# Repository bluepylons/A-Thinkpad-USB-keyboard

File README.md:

# Work in Progress

## Note January 21, 2025: the downstream USB-C port likely violates USB-C spec since it provides 5V all the time, instead of only when CC resistors are detected.

# About

This is a project attempting to make a USB keyboard/Trackpoint controller and enclosure for the non-chiclet Thinkpad keyboard (from the 10/20 generation, such as the T410, W520, etc.). These were, in my opinion, the best Thinkpad keyboards ever made.

# Controller

The current plan is to use an RP2040 microcontroller running QMK to handle the key matrix scanning and Trackpoint. I would also like to add a USB 2.0 hub.

# Future goals

I would like to eventually adapt this keyboard to be used on the Framework 13 laptop, which would require designing a custom lower chassis for the Framework laptop. That is well in the future, but the engineering required for this project lays much of the groundwork for that project.

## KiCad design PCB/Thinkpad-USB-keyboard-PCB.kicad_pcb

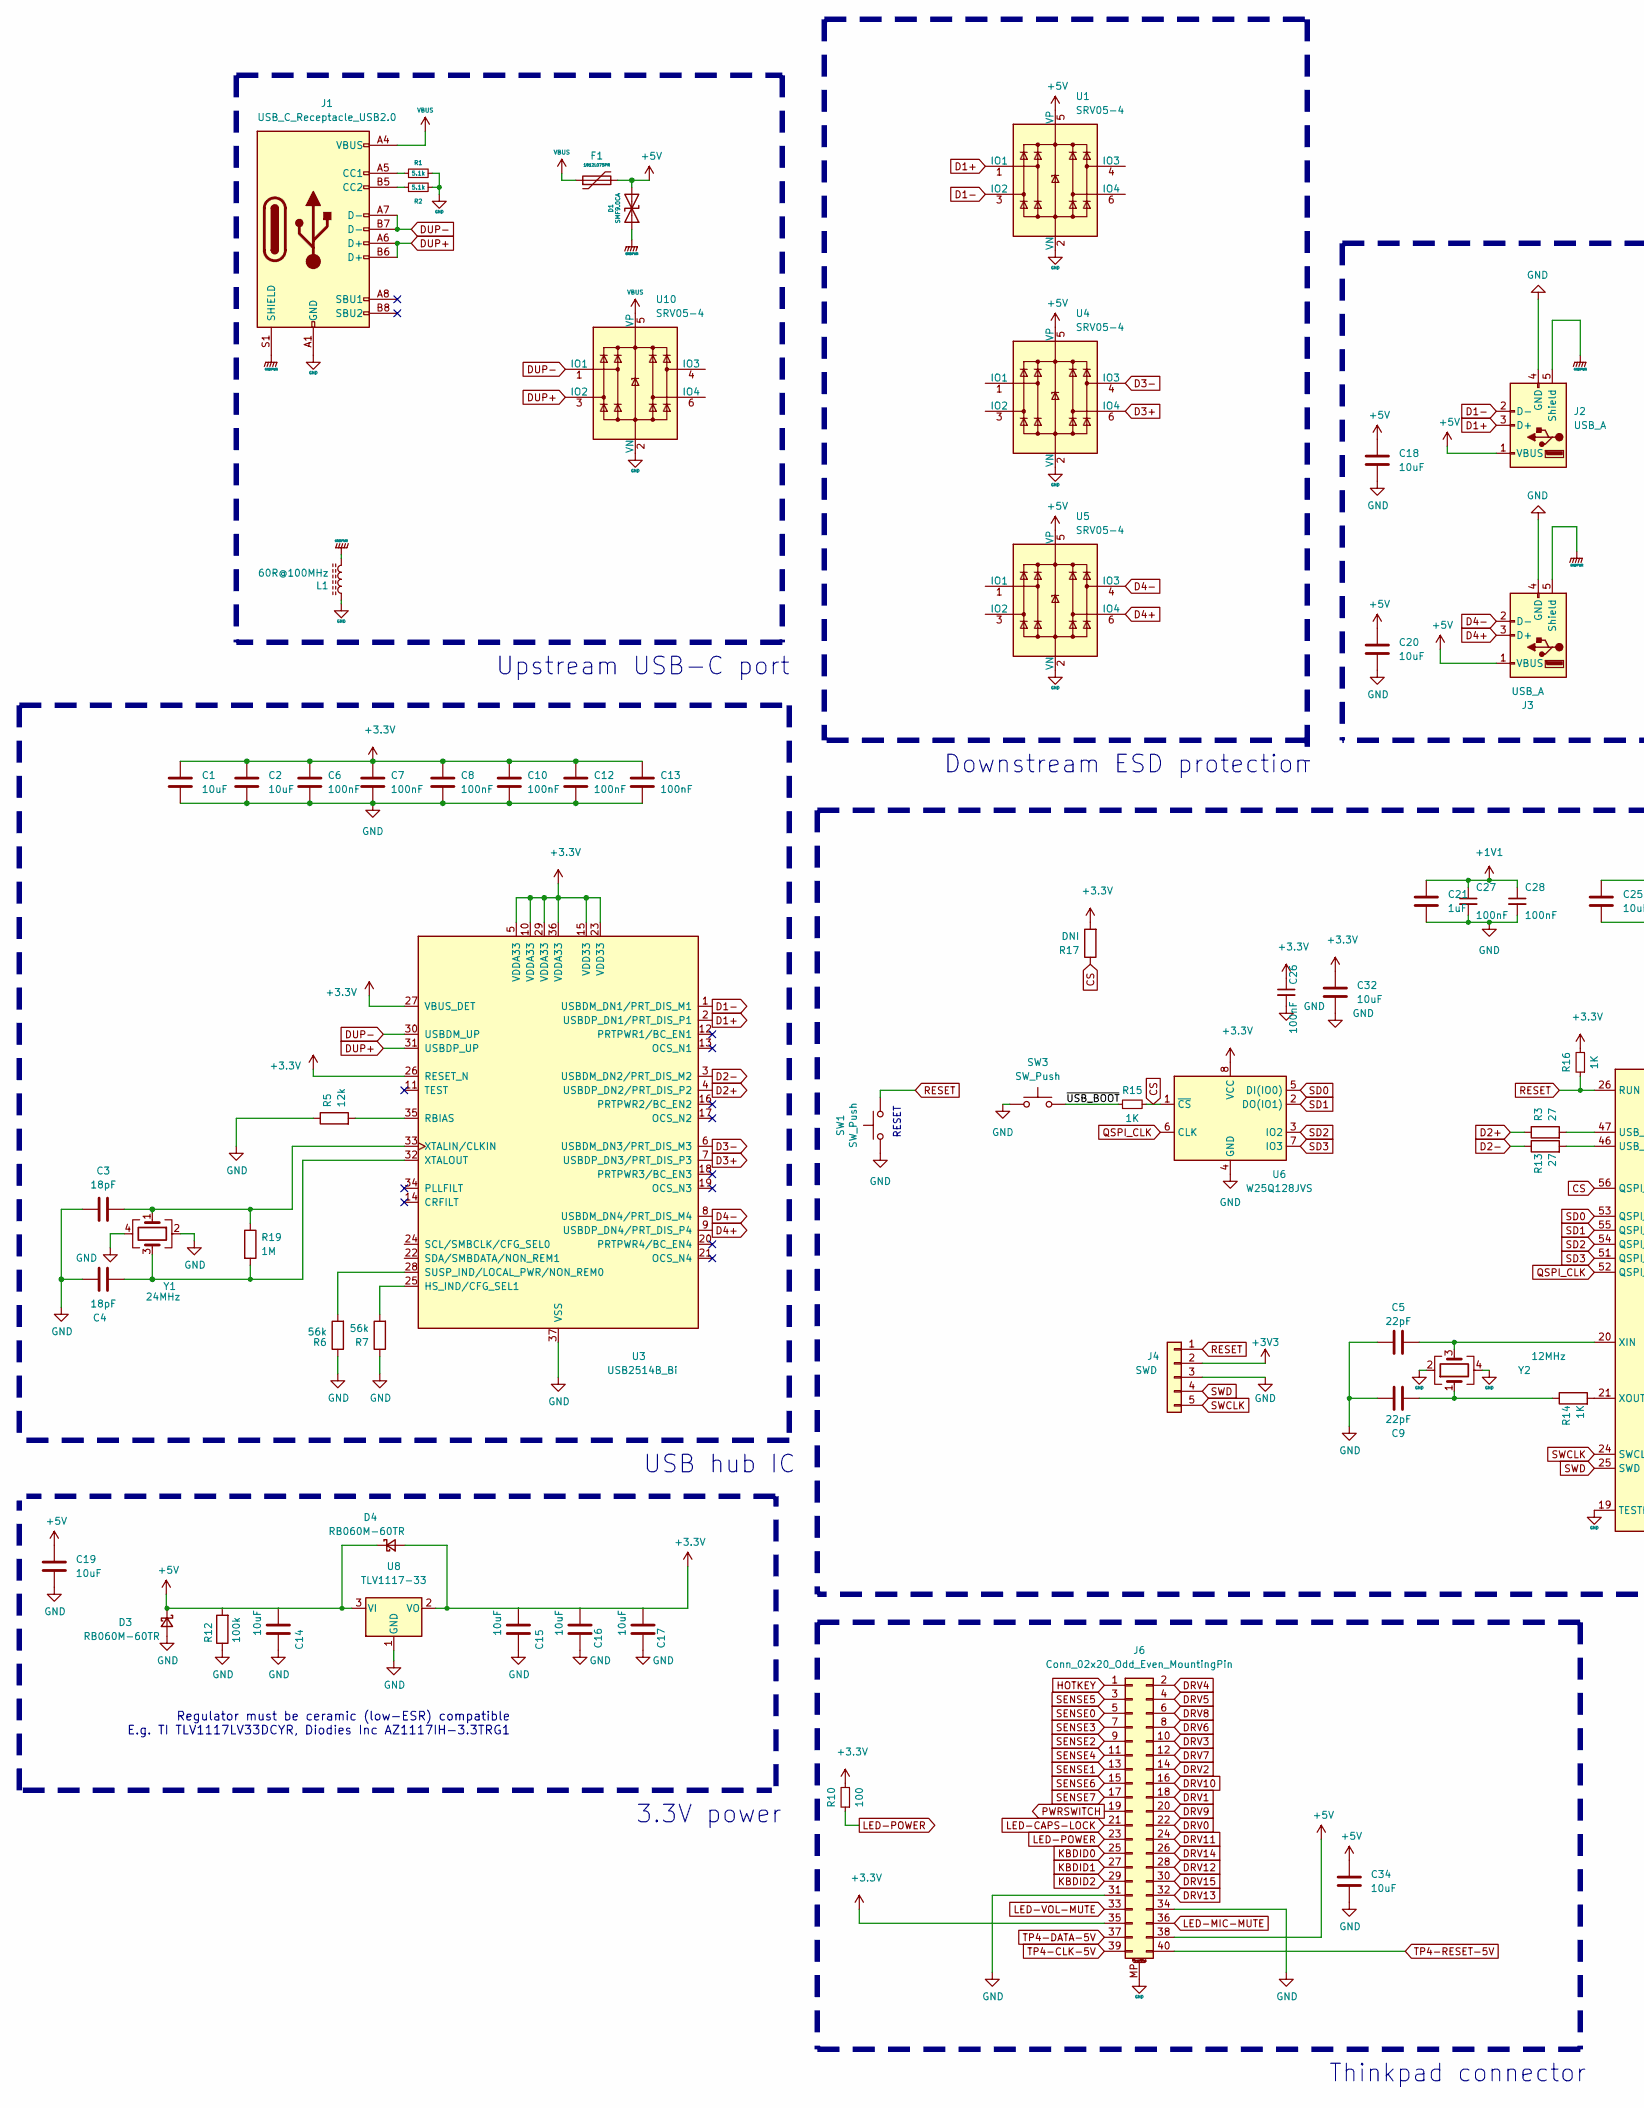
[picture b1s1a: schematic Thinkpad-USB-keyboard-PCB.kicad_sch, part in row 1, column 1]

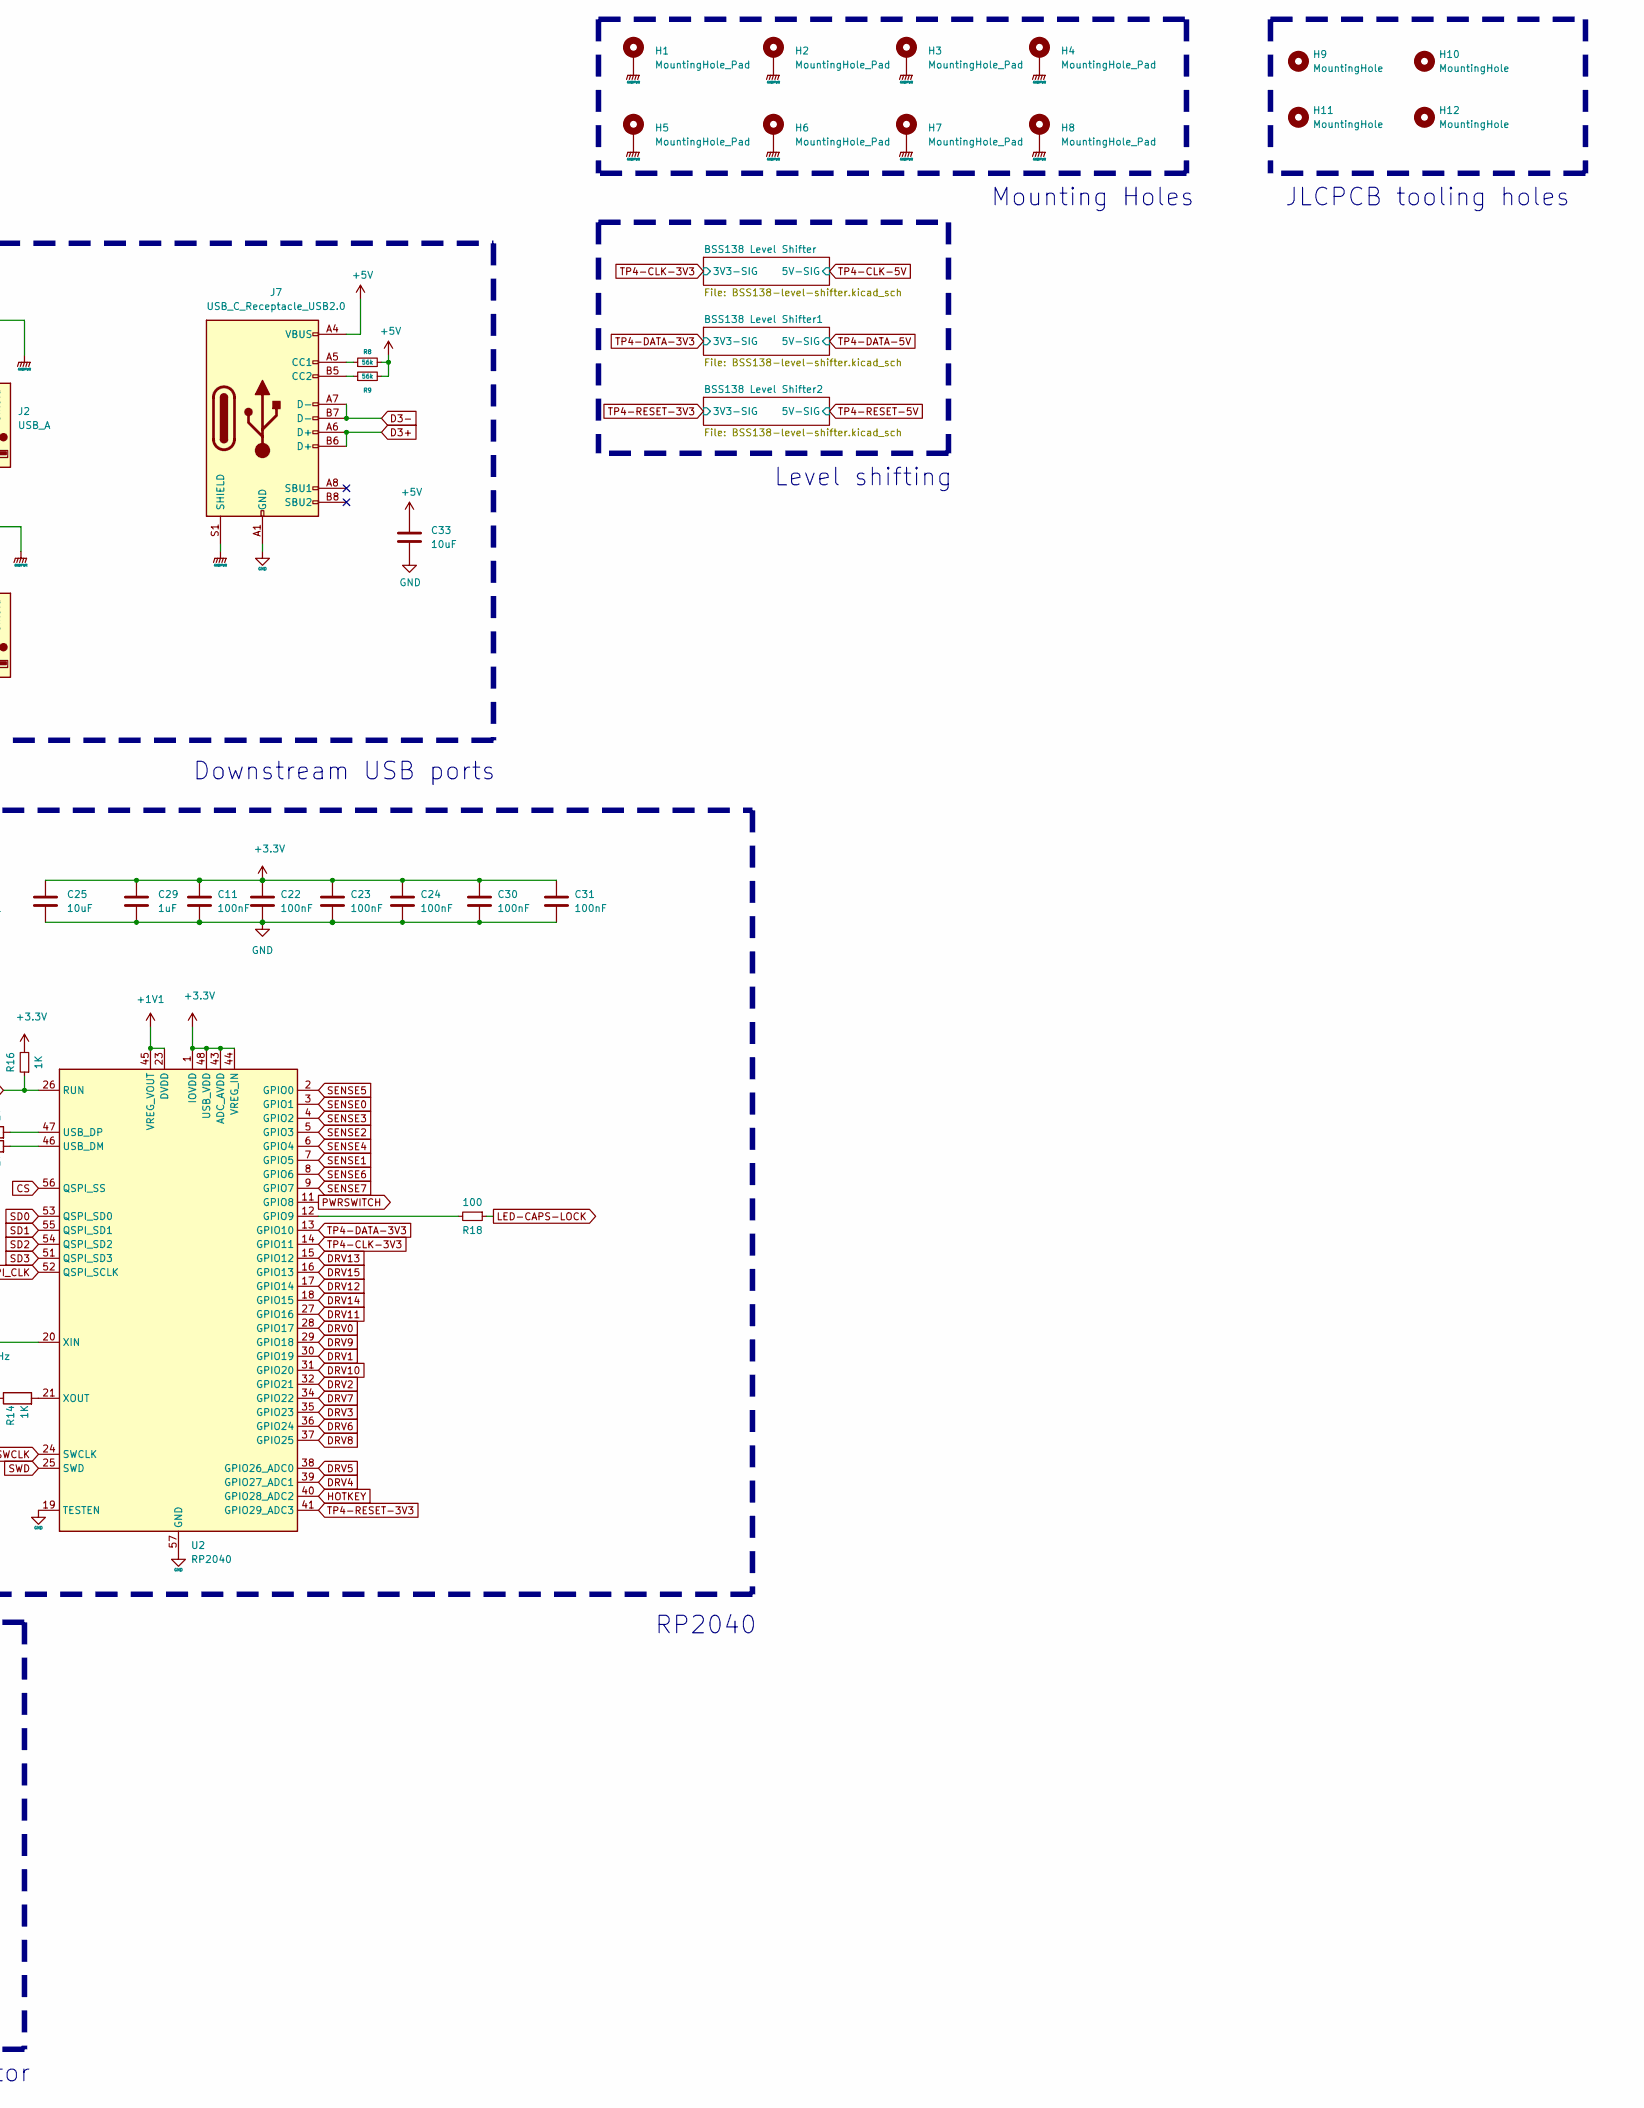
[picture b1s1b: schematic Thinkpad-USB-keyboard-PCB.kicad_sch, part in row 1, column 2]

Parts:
C1, C2, C14, C15, C16, C17, C18, C19, C20, C25, C32, C33, C34: 10uF; C_1206_3216Metric_Pad1.33x1.80mm_HandSolder
C3, C4: 18pF; C_0402_1005Metric_Pad0.74x0.62mm_HandSolder
C5, C9: 22pF; C_0402_1005Metric_Pad0.74x0.62mm_HandSolder
C6, C7, C8, C10, C11, C12, C13, C22, C23, C24, C30, C31: 100nF; C_0402_1005Metric_Pad0.74x0.62mm_HandSolder
C21, C29: 1uF; C_0603_1608Metric_Pad1.08x0.95mm_HandSolder
C26, C27, C28: 100nF; C_0402_1005Metric_Pad0.74x0.62mm_HandSolder; LCSC C1525
D1: SMF9.0CA; D_SOD-123; Manufacturer Part No SMF9.0CA; LCSC Part No C123799
D3, D4: RB060M-60TR; D_SOD-123
F1: 1812L075PR; Fuse_1812_4532Metric_Pad1.30x3.40mm_HandSolder; Manufacturer Part No ASMD1206-150; LCSC Part No C135342
H1, H2, H3, H4, H5, H6, H7, H8: MountingHole_Pad; MountingHole_3.2mm_M3_ISO7380_Pad
H9, H10, H11, H12: MountingHole; JLCPCB-tooling-hole
J1, J7: USB_C_Receptacle_USB2.0; USB_C_Receptacle_HRO_TYPE-C-31-M-12; LCSC C165948
J2, J3: USB_A; USB_A_Molex_67643_Horizontal
J4: SWD; PinSocket_1x05_P2.54mm_Vertical
J6: Conn_02x20_Odd_Even_MountingPin; Molex Slimstack 54363-0489
L1: 60R@100MHz; L_1206_3216Metric; Manufacturer Part No MLB3216-600P4A(f); LCSC Part No C33600
R1, R2: 5.1k; R_0805_2012Metric_Pad1.20x1.40mm_HandSolder
R3, R13: 27; C_0402_1005Metric_Pad0.74x0.62mm_HandSolder
R5: 12k; R_0805_2012Metric_Pad1.20x1.40mm_HandSolder
R6, R7, R8, R9: 56k; R_0805_2012Metric_Pad1.20x1.40mm_HandSolder
R10, R18: 100; R_0805_2012Metric_Pad1.20x1.40mm_HandSolder; LCSC C11702
R12: 100k; R_0805_2012Metric_Pad1.20x1.40mm_HandSolder
R14: 1K; R_0805_2012Metric_Pad1.20x1.40mm_HandSolder
R15, R16: 1K; R_0805_2012Metric_Pad1.20x1.40mm_HandSolder; LCSC C11702
R17: DNI; C_0805_2012Metric_Pad1.18x1.45mm_HandSolder
R19: 1M; R_0805_2012Metric_Pad1.20x1.40mm_HandSolder
SW1, SW3: SW_Push; SW_PUSH_6mm_H5mm
U1, U4, U5, U10: SRV05-4; SOT-23-6
U2: RP2040; QFN-56-1EP_7x7mm_P0.4mm_EP3.2x3.2mm
U3: USB2514B_Bi; QFN-36-1EP_6x6mm_P0.5mm_EP3.7x3.7mm
U6: W25Q128JVS; SOIC-8_5.23x5.23mm_P1.27mm; LCSC C131025
U8: TLV1117-33; SOT-223-3_TabPin2
Y1: 24MHz; Crystal_SMD_3225-4Pin_3.2x2.5mm_HandSoldering
Y2: 12MHz; Crystal_SMD_3225-4Pin_3.2x2.5mm_HandSoldering

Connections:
+1V1: C21.1, C27.1, C28.1, U2.23 (DVDD), U2.45 (VREG_VOUT), U2.50 (DVDD)
+5V: C14.1, C18.1, C19.1, C20.1, C33.1, C34.1, D1.2 (A2), D3.1 (K), D4.1 (K), F1.2, J2.1 (VBUS), J3.1 (VBUS), J6.38, J7.A4 (VBUS), J7.A9 (VBUS), J7.B4 (VBUS), J7.B9 (VBUS), R8.2, R9.2, R12.2, U1.5 (VP), U4.5 (VP), U5.5 (VP), U8.3 (VI); also elsewhere on the board
/~USB_BOOT: R15.1, SW3.2
CS: R15.2, R17.1, U2.56 (QSPI_SS), U6.1 (~CS)
D1+: J2.3 (D+), U1.1 (IO1), U3.2 (USBDP_DN1/PRT_DIS_P1)
D1-: J2.2 (D-), U1.3 (IO2), U3.1 (USBDM_DN1/PRT_DIS_M1)
D2+: R3.1, U3.4 (USBDP_DN2/PRT_DIS_P2)
D2-: R13.1, U3.3 (USBDM_DN2/PRT_DIS_M2)
D3+: J7.A6 (D+), J7.B6 (D+), U3.7 (USBDP_DN3/PRT_DIS_P3), U4.6 (IO4)
D3-: J7.A7 (D-), J7.B7 (D-), U3.6 (USBDM_DN3/PRT_DIS_M3), U4.4 (IO3)
D4+: J3.3 (D+), U3.9 (USBDP_DN4/PRT_DIS_P4), U5.6 (IO4)
D4-: J3.2 (D-), U3.8 (USBDM_DN4/PRT_DIS_M4), U5.4 (IO3)
DRV0: J6.22, U2.28 (GPIO17)
DRV1: J6.18, U2.30 (GPIO19)
DRV2: J6.14, U2.32 (GPIO21)
DRV3: J6.10, U2.35 (GPIO23)
DRV4: J6.2, U2.39 (GPIO27_ADC1)
DRV5: J6.4, U2.38 (GPIO26_ADC0)
DRV6: J6.8, U2.36 (GPIO24)
DRV7: J6.12, U2.34 (GPIO22)
DRV8: J6.6, U2.37 (GPIO25)
DRV9: J6.20, U2.29 (GPIO18)
DRV10: J6.16, U2.31 (GPIO20)
DRV11: J6.24, U2.27 (GPIO16)
DRV12: J6.28, U2.17 (GPIO14)
DRV13: J6.32, U2.15 (GPIO12)
DRV14: J6.26, U2.18 (GPIO15)
DRV15: J6.30, U2.16 (GPIO13)
DUP+: J1.A6 (D+), J1.B6 (D+), U3.31 (USBDP_UP), U10.3 (IO2)
DUP-: J1.A7 (D-), J1.B7 (D-), U3.30 (USBDM_UP), U10.1 (IO1)
GND: C1.2, C2.2, C3.1, C4.1, C5.1, C6.2, C7.2, C8.2, C9.1, C10.2, C11.2, C12.2, C13.2, C14.2, C15.2, C16.2, C17.2, C18.2, C19.2, C20.2, C21.2, C22.2, C23.2, C24.2, C25.2, C26.2, C27.2, C28.2, C29.2, C30.2, C31.2, C32.2, C33.2, C34.2, D3.2 (A), J1.A1 (GND), J1.A12 (GND), J1.B1 (GND), J1.B12 (GND), J2.4 (GND), J3.4 (GND), J4.3, J6.31, J6.34, J6.MP (MountPin), J7.A1 (GND), J7.A12 (GND), J7.B1 (GND), J7.B12 (GND), L1.1, R1.2, R2.2, R5.1, R6.1, R7.1, R12.1, SW1.1, SW3.1, U1.2 (VN), U2.19 (TESTEN), U2.57 (GND), U3.37 (VSS), U4.2 (VN), U5.2 (VN), U6.4 (GND), U8.1 (GND), U10.2 (VN), Y1.2, Y1.4, Y2.2, Y2.4
GNDPWR: D1.1 (A1), H1.1, H2.1, H3.1, H4.1, H5.1, H6.1, H7.1, H8.1, J1.S1 (SHIELD), J2.5 (Shield), J3.5 (Shield), J7.S1 (SHIELD), L1.2
HOTKEY: J6.1, U2.40 (GPIO28_ADC2)
KBDID0: J6.25
KBDID1: J6.27
KBDID2: J6.29
LED-CAPS-LOCK: J6.21, R18.1
LED-MIC-MUTE: J6.36
LED-POWER: J6.23, R10.1
LED-VOL-MUTE: J6.33
unnamed: C9.2, R14.1, Y2.1
unnamed: J1.A5 (CC1), R1.1
unnamed: J1.B5 (CC2), R2.1
unnamed: J7.A5 (CC1), R8.1
unnamed: J7.B5 (CC2), R9.1
unnamed: R18.2, U2.12 (GPIO9)
unnamed: R13.2, U2.46 (USB_DM)
unnamed: R3.2, U2.47 (USB_DP)
unnamed: C5.2, U2.20 (XIN), Y2.3
unnamed: R14.2, U2.21 (XOUT)
unnamed: R7.2, U3.25 (HS_IND/CFG_SEL1)
unnamed: R5.2, U3.35 (RBIAS)
unnamed: R6.2, U3.28 (SUSP_IND/LOCAL_PWR/NON_REM0)
unnamed: C3.2, R19.1, U3.33 (XTALIN/CLKIN), Y1.1
unnamed: C4.2, R19.2, U3.32 (XTALOUT), Y1.3
PWRSWITCH: J6.19, U2.11 (GPIO8)
QSPI_CLK: U2.52 (QSPI_SCLK), U6.6 (CLK)
RESET: J4.1, R16.1, SW1.2, U2.26 (RUN)
SD0: U2.53 (QSPI_SD0), U6.5 (DI(IO0))
SD1: U2.55 (QSPI_SD1), U6.2 (DO(IO1))
SD2: U2.54 (QSPI_SD2), U6.3 (IO2)
SD3: U2.51 (QSPI_SD3), U6.7 (IO3)
SENSE0: J6.5, U2.3 (GPIO1)
SENSE1: J6.13, U2.7 (GPIO5)
SENSE2: J6.9, U2.5 (GPIO3)
SENSE3: J6.7, U2.4 (GPIO2)
SENSE4: J6.11, U2.6 (GPIO4)
SENSE5: J6.3, U2.2 (GPIO0)
SENSE6: J6.15, U2.8 (GPIO6)
SENSE7: J6.17, U2.9 (GPIO7)
SWCLK: J4.5, U2.24 (SWCLK)
SWD: J4.4, U2.25 (SWD)
TP4-CLK-3V3: U2.14 (GPIO11); also elsewhere on the board
TP4-CLK-5V: J6.39; also elsewhere on the board
TP4-DATA-3V3: U2.13 (GPIO10); also elsewhere on the board
TP4-DATA-5V: J6.37; also elsewhere on the board
TP4-RESET-3V3: U2.41 (GPIO29_ADC3); also elsewhere on the board
TP4-RESET-5V: J6.40; also elsewhere on the board
VBUS: F1.1, J1.A4 (VBUS), J1.A9 (VBUS), J1.B4 (VBUS), J1.B9 (VBUS), U10.5 (VP)

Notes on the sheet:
RP2040
JLCPCB tooling holes
Downstream USB ports
Upstream USB-C port
Mounting Holes
USB hub IC
Regulator must be ceramic (low-ESR) compatible E.g. TI TLV1117LV33DCYR, Diodies Inc AZ1117IH-3.3TRG1
Thinkpad connector
Level shifting
RESET
Downstream ESD protection
3.3V power

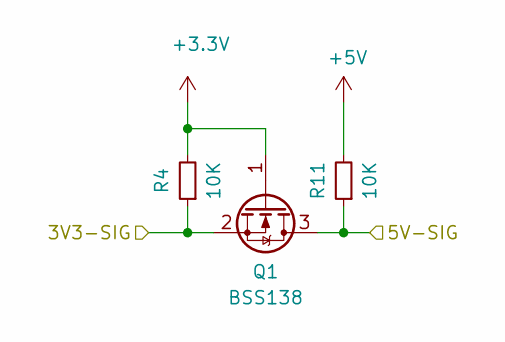
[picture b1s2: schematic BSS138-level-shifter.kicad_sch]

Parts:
Q1: BSS138; SOT-23
R4, R11: 10K; R_0603_1608Metric_Pad0.98x0.95mm_HandSolder; LCSC C11702

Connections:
+5V: R11.2; also elsewhere on the board
TP4-CLK-3V3: Q1.2 (S), R4.1; also elsewhere on the board
TP4-CLK-5V: Q1.3 (D), R11.1; also elsewhere on the board

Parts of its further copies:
Q2, Q3: BSS138; SOT-23
R20, R21, R22, R23: 10K; R_0603_1608Metric_Pad0.98x0.95mm_HandSolder; LCSC C11702

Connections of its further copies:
+5V: R21.2, R23.2; also elsewhere on the board
TP4-DATA-3V3: Q2.2 (S), R20.1; also elsewhere on the board
TP4-DATA-5V: Q2.3 (D), R21.1; also elsewhere on the board
TP4-RESET-3V3: Q3.2 (S), R22.1; also elsewhere on the board
TP4-RESET-5V: Q3.3 (D), R23.1; also elsewhere on the board

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
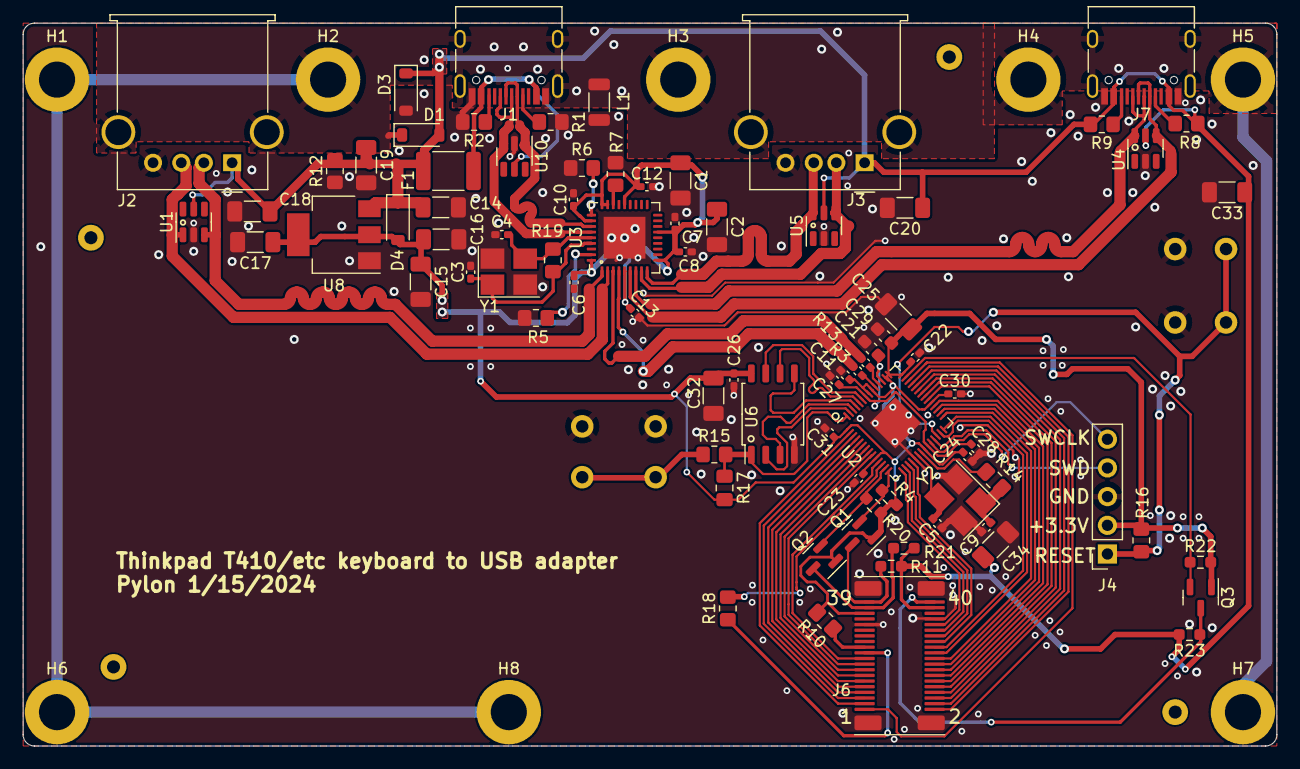
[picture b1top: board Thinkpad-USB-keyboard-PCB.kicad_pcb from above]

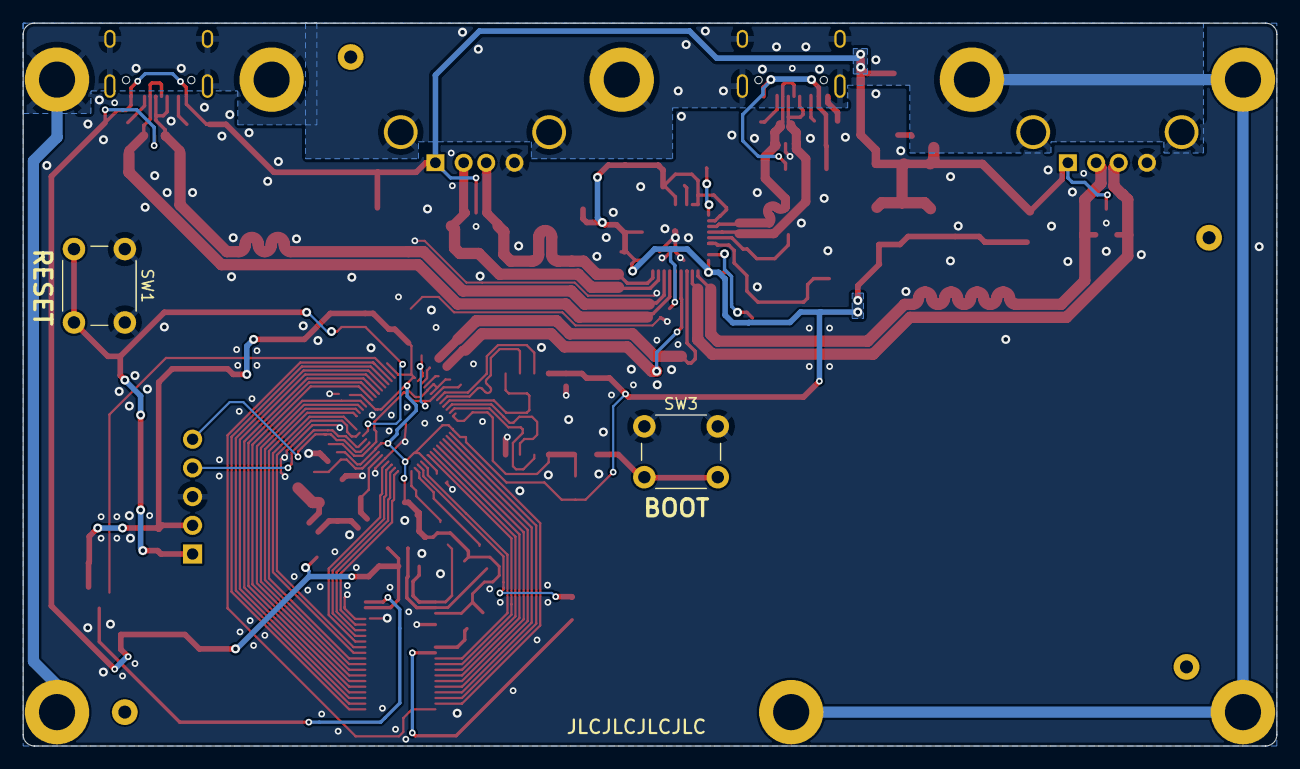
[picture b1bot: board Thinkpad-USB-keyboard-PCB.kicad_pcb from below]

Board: 2 copper layers, 111.0 x 64.0 mm, 95 parts (2 on the bottom side), 75 nets.

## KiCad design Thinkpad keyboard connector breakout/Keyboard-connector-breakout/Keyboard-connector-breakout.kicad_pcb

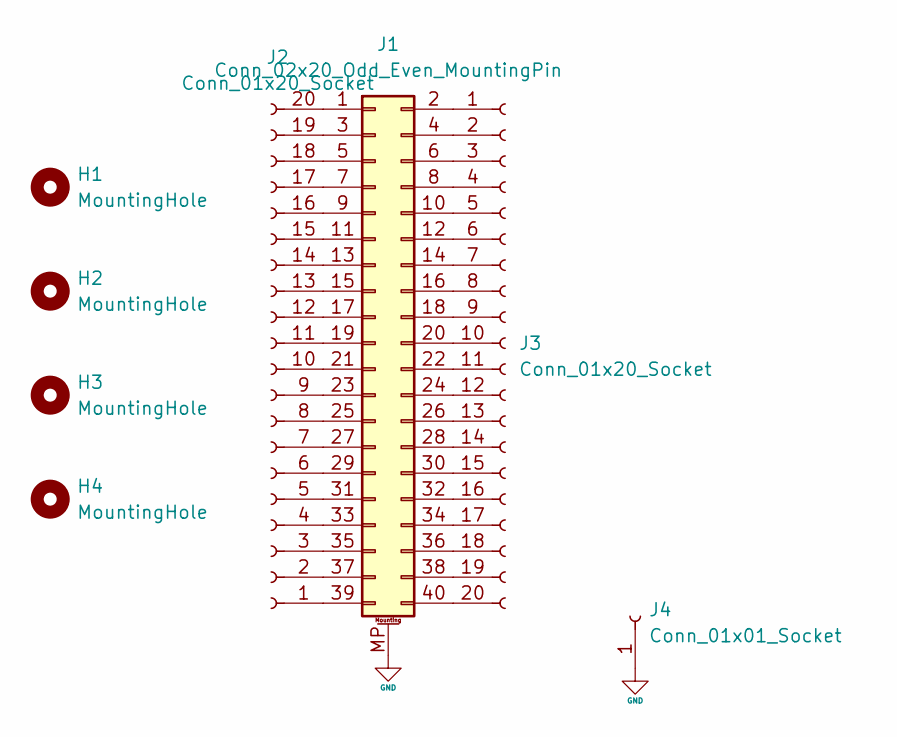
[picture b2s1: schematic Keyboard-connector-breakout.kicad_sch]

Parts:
H1, H2, H3, H4: MountingHole; MountingHole_3.2mm_M3_ISO7380
J1: Conn_02x20_Odd_Even_MountingPin; Molex Slimstack 54363-0489
J2, J3: Conn_01x20_Socket; PinSocket_1x20_P2.54mm_Vertical
J4: Conn_01x01_Socket; PinHeader_1x01_P2.54mm_Vertical

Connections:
GND: J1.MP (MountPin), J4.1
unnamed: J1.1, J2.20
unnamed: J1.2, J3.1
unnamed: J1.3, J2.19
unnamed: J1.4, J3.2
unnamed: J1.5, J2.18
unnamed: J1.6, J3.3
unnamed: J1.7, J2.17
unnamed: J1.8, J3.4
unnamed: J1.9, J2.16
unnamed: J1.10, J3.5
unnamed: J1.11, J2.15
unnamed: J1.12, J3.6
unnamed: J1.13, J2.14
unnamed: J1.14, J3.7
unnamed: J1.15, J2.13
unnamed: J1.16, J3.8
unnamed: J1.17, J2.12
unnamed: J1.18, J3.9
unnamed: J1.19, J2.11
unnamed: J1.20, J3.10
unnamed: J1.21, J2.10
unnamed: J1.22, J3.11
unnamed: J1.23, J2.9
unnamed: J1.24, J3.12
unnamed: J1.25, J2.8
unnamed: J1.26, J3.13
unnamed: J1.27, J2.7
unnamed: J1.28, J3.14
unnamed: J1.29, J2.6
unnamed: J1.30, J3.15
unnamed: J1.31, J2.5
unnamed: J1.32, J3.16
unnamed: J1.33, J2.4
unnamed: J1.34, J3.17
unnamed: J1.35, J2.3
unnamed: J1.36, J3.18
unnamed: J1.37, J2.2
unnamed: J1.38, J3.19
unnamed: J1.39, J2.1
unnamed: J1.40, J3.20

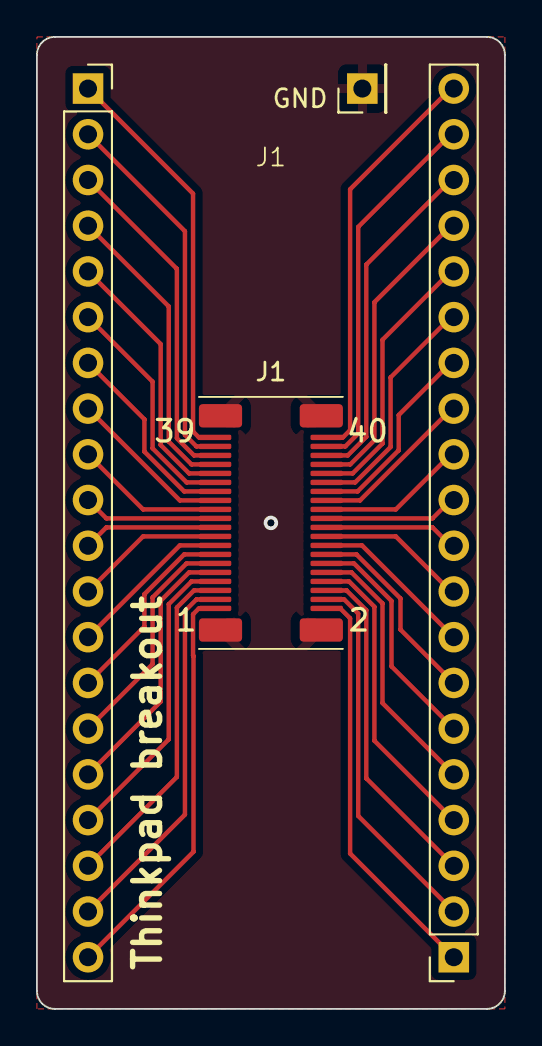
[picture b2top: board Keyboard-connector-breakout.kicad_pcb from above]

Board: 2 copper layers, 26.0 x 54.0 mm, 8 parts (0 on the bottom side), 41 nets.

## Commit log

2024-01-06 More work
2024-01-06 Clarified this is a work in progress
2024-01-07 Made a breakout board for the Thinkpad keyboard connector
2024-01-11 More layout work
2024-01-13 Fixed some errors
2024-01-15 Finalized initial version
2024-01-15 finalized files
2024-03-01 Added license; more development work
